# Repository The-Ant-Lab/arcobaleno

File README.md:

# Arcobaleno<br/>A micropython development board made with The Ant.

This is our first complete project made with The Ant CNC machine.  
It is a development board designed by us and intended to be used with micropython.  

In this repository and in this video [The Ant + Micropython = ARCOBALENO](https://youtu.be/vV_R-Mp-2kI), you will find all the related information.  

If you want to realize the board with The Ant see the hardware folder.  
If you have already built the board and you want to use it see the firmware folder.  

If you liked this project and you want to help us develop new interesting projects, please consider donating using the paypal button here:

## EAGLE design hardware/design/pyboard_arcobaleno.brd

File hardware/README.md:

The hardware section is structured as follows:

- design, that contains the schematic and the board layout;
- cam, that contains the CAM outputs of the whole board, comprising gerbers and drill files.
- gcodes, that contains all the gcodes needed to execute the board machining with The Ant (see [here](https://www.youtube.com/channel/UCX44z-SSL7LzcB4xxgUdHHA)).

Before using the gcode files, read carefully the README in the gcodes folder.

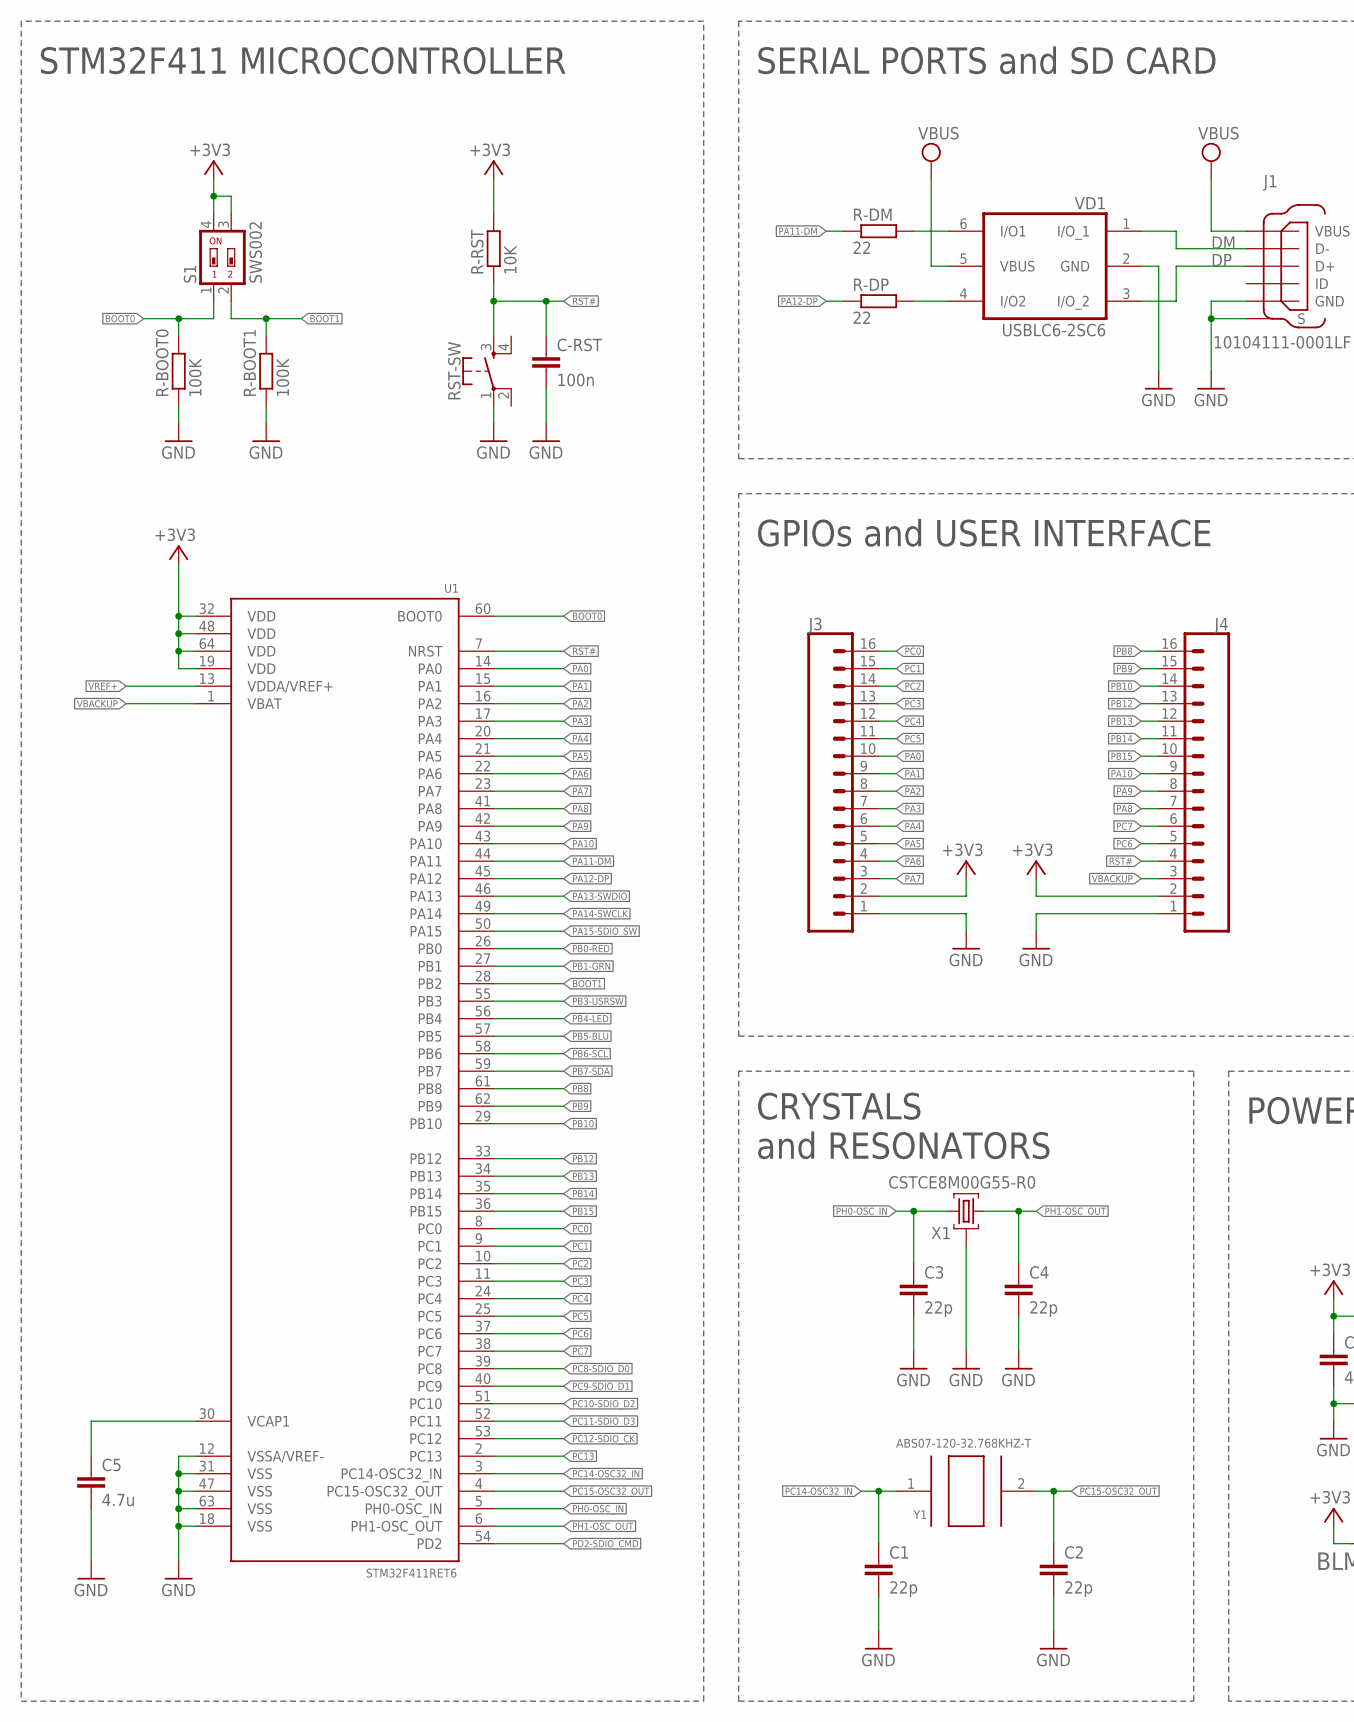
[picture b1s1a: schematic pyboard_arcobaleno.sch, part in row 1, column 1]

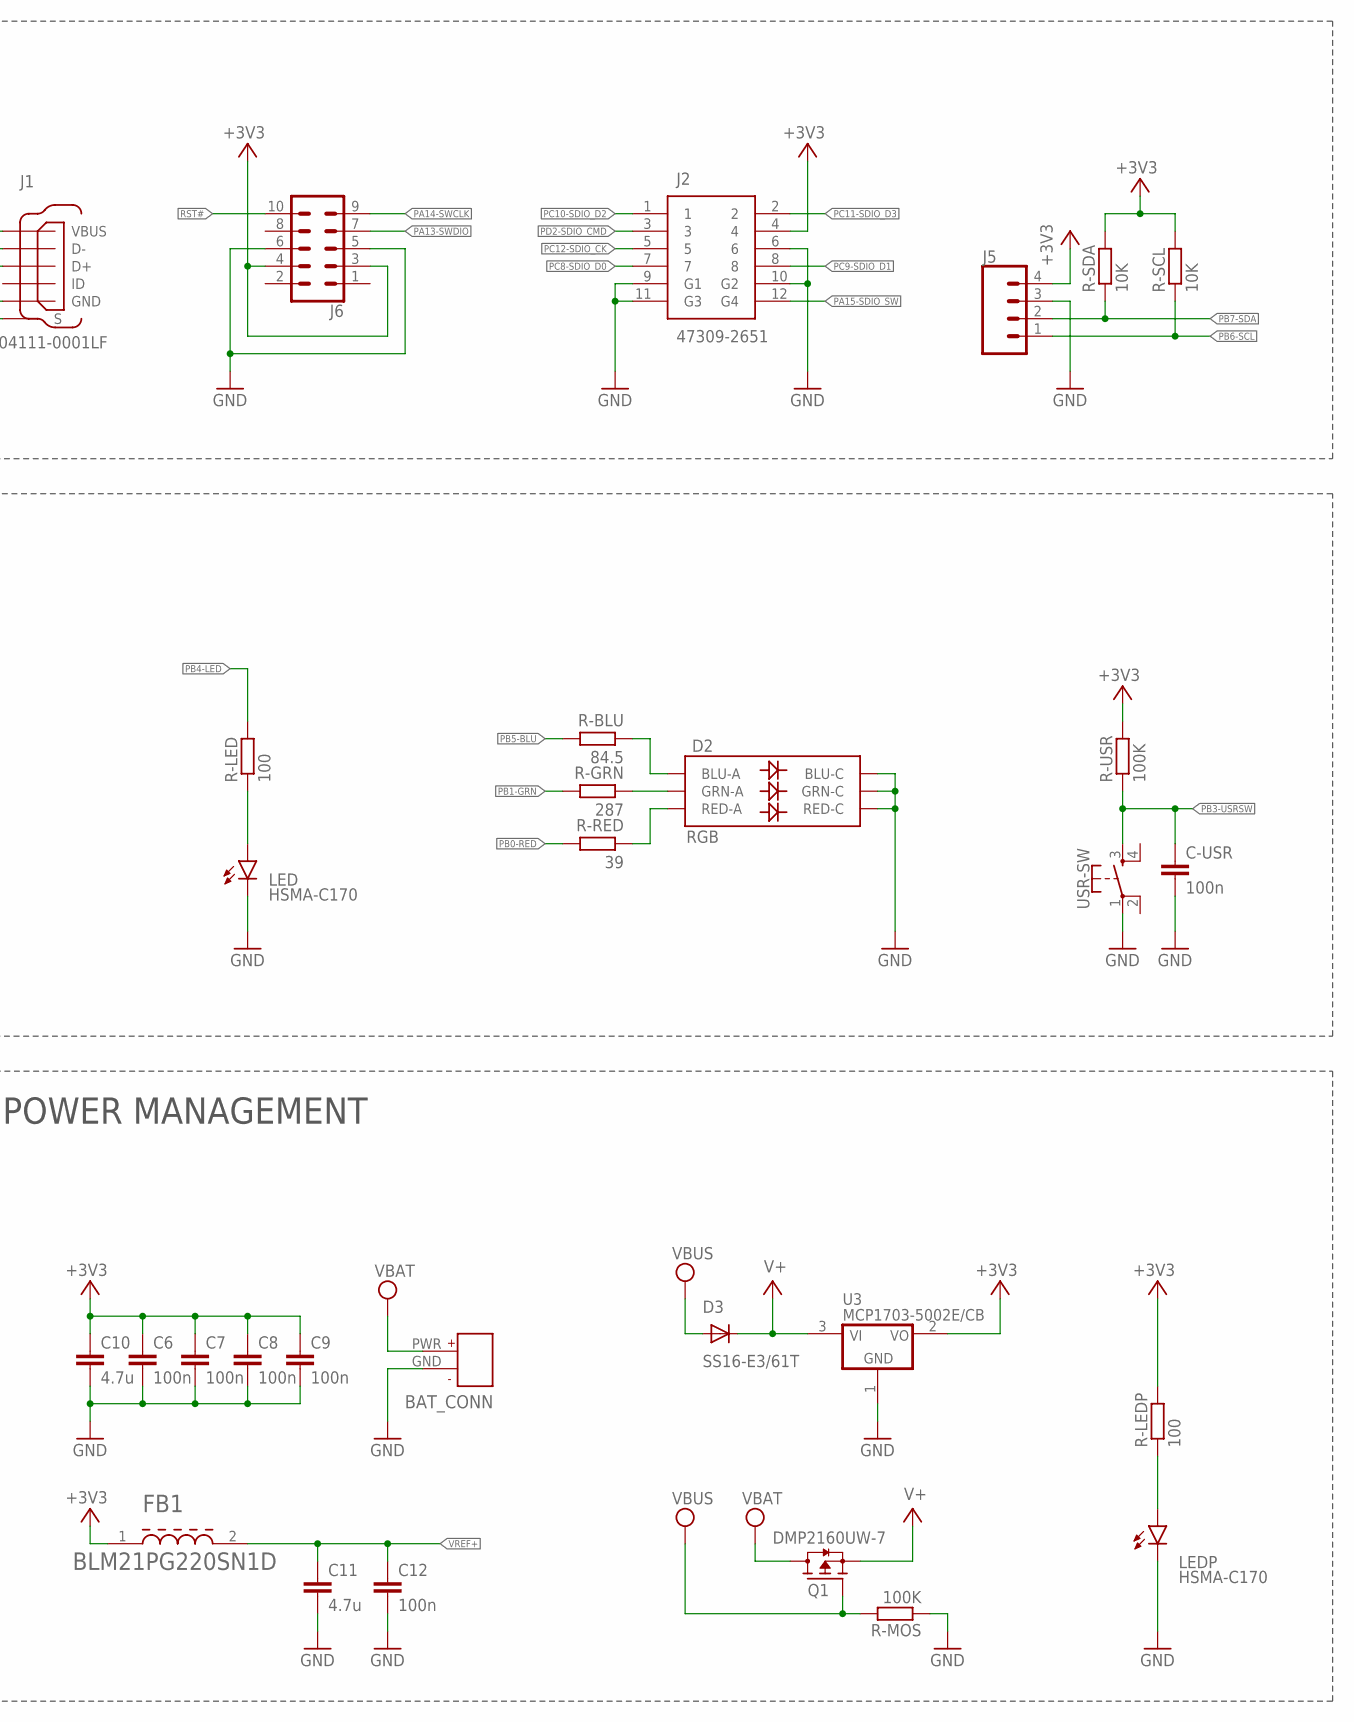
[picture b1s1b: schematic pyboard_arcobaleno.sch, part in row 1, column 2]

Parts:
BAT_CONN: JST_PH_2PIN
C1, C2, C3, C4: 22p; C0603
C5, C10, C11: 4.7u; C1608
C6, C7, C8, C9, C12: 100n; C0603
C-RST: 100n; C0603
C-USR: 100n; C0603
D2: RGB; PLCC-6-LED
D3: SS16-E3/61T; DO214AA
FB1: MURATA_BLM21PG220SN1DMURATA_BLM21PG220SN1D_0_0; MURATA_BLM21PG220SN1D_0
J1: 10104111-0001LF; FRAMATOME_10104111-0001LF
J2: 47309-2651
J3, J4: CONN_16; 1X16
J5: CONN_04; 1X04
J6: CONN_05X2PTH; 2X5
LED: HSMA-C170; CHIPLED_0805
LEDP: HSMA-C170; CHIPLED_0805
Q1: DMP2160UW-7; SOT65P210X110-3N
R-BLU: 84.5; R0603
R-BOOT0, R-BOOT1: 100K; R0603
R-DM: 22; R0603
R-DP: 22; R0603
R-GRN: 287; R0603
R-LED: 100; R0603
R-LEDP: 100; R0603
R-MOS: 100K; R0603
R-RED: 39; R0603
R-RST: 10K; R0603
R-SCL: 10K; R0603
R-SDA: 10K; R0603
R-USR: 100K; R0603
RST-SW: MOMENTARY-SWITCH-SPST-2-SMD-5.2MM; TACTILE_SWITCH_SMD_5.2MM
S1: SWS002; SMS-002
U1: STM32F411RET6; QFP50P1200X1200X160-64N
U3: MCP1703-5002E/CB; SOT23A_MICROCHIP_CB
USR-SW: MOMENTARY-SWITCH-SPST-2-SMD-5.2MM; TACTILE_SWITCH_SMD_5.2MM
VD1: USBLC6-2SC6; SOT-23-6L
X1: CSTCE8M00G55-R0
Y1: ABS07-120-32.768KHZ-T; XTAL_ABS07-120-32.768KHZ-T

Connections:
+3V3: C6.1, C7.1, C8.1, C9.1, C10.1, FB1.1, J2.4, J3.2, J4.2, J5.4, J6.3, J6.4, R-LEDP.2, R-RST.2, R-SCL.2, R-SDA.2, R-USR.2, S1.3, S1.4, U1.19 (VDD), U1.32 (VDD), U1.48 (VDD), U1.64 (VDD), U3.2 (VO)
BOOT0: R-BOOT0.2, S1.1, U1.60 (BOOT0)
BOOT1: R-BOOT1.2, S1.2, U1.28 (PB2)
DM: J1.2 (D-), VD1.1 (I/O_1)
DP: J1.3 (D+), VD1.3 (I/O_2)
GND: BAT_CONN.GND, C1.2, C2.2, C3.2, C4.2, C5.2, C6.2, C7.2, C8.2, C9.2, C10.2, C11.2, C12.2, C-RST.2, C-USR.2, D2.CB (BLU-C), D2.CG (GRN-C), D2.CR (RED-C), J1.5 (GND), J1.6 (S), J1.7 (S), J1.8 (S), J1.9 (S), J2.6, J2.9 (G1), J2.10 (G2), J2.11 (G3), J3.1, J4.1, J5.3, J6.5, J6.6, LED.C, LEDP.C, R-BOOT0.1, R-BOOT1.1, R-MOS.1, RST-SW.1, U1.12 (VSSA/VREF-), U1.18 (VSS), U1.31 (VSS), U1.47 (VSS), U1.63 (VSS), U3.1 (GND), USR-SW.1, VD1.2 (GND), X1.2 (GND)
unnamed: C5.1, U1.30 (VCAP1)
unnamed: R-DM.2, VD1.6 (I/O1)
unnamed: R-DP.2, VD1.4 (I/O2)
unnamed: LED.A, R-LED.1
unnamed: LEDP.A, R-LEDP.1
unnamed: D2.AB (BLU-A), R-BLU.1
unnamed: D2.AG (GRN-A), R-GRN.1
unnamed: D2.AR (RED-A), R-RED.1
PA0: J3.10, U1.14 (PA0)
PA1: J3.9, U1.15 (PA1)
PA2: J3.8, U1.16 (PA2)
PA3: J3.7, U1.17 (PA3)
PA4: J3.6, U1.20 (PA4)
PA5: J3.5, U1.21 (PA5)
PA6: J3.4, U1.22 (PA6)
PA7: J3.3, U1.23 (PA7)
PA8: J4.7, U1.41 (PA8)
PA9: J4.8, U1.42 (PA9)
PA10: J4.9, U1.43 (PA10)
PA11-DM: R-DM.1, U1.44 (PA11)
PA12-DP: R-DP.1, U1.45 (PA12)
PA13-SWDIO: J6.7, U1.46 (PA13)
PA14-SWCLK: J6.9, U1.49 (PA14)
PA15-SDIO_SW: J2.12 (G4), U1.50 (PA15)
PB0-RED: R-RED.2, U1.26 (PB0)
PB1-GRN: R-GRN.2, U1.27 (PB1)
PB3-USRSW: C-USR.1, R-USR.1, U1.55 (PB3), USR-SW.3
PB4-LED: R-LED.2, U1.56 (PB4)
PB5-BLU: R-BLU.2, U1.57 (PB5)
PB6-SCL: J5.1, R-SCL.1, U1.58 (PB6)
PB7-SDA: J5.2, R-SDA.1, U1.59 (PB7)
PB8: J4.16, U1.61 (PB8)
PB9: J4.15, U1.62 (PB9)
PB10: J4.14, U1.29 (PB10)
PB12: J4.13, U1.33 (PB12)
PB13: J4.12, U1.34 (PB13)
PB14: J4.11, U1.35 (PB14)
PB15: J4.10, U1.36 (PB15)
PC0: J3.16, U1.8 (PC0)
PC1: J3.15, U1.9 (PC1)
PC2: J3.14, U1.10 (PC2)
PC3: J3.13, U1.11 (PC3)
PC4: J3.12, U1.24 (PC4)
PC5: J3.11, U1.25 (PC5)
PC6: J4.5, U1.37 (PC6)
PC7: J4.6, U1.38 (PC7)
PC8-SDIO_D0: J2.7, U1.39 (PC8)
PC9-SDIO_D1: J2.8, U1.40 (PC9)
PC10-SDIO_D2: J2.1, U1.51 (PC10)
PC11-SDIO_D3: J2.2, U1.52 (PC11)
PC12-SDIO_CK: J2.5, U1.53 (PC12)
PC13: U1.2 (PC13)
PC14-OSC32_IN: C1.1, U1.3 (PC14-OSC32_IN), Y1.1
PC15-OSC32_OUT: C2.1, U1.4 (PC15-OSC32_OUT), Y1.2
PD2-SDIO_CMD: J2.3, U1.54 (PD2)
PH0-OSC_IN: C3.1, U1.5 (PH0-OSC_IN), X1.1 (INPUT)
PH1-OSC_OUT: C4.1, U1.6 (PH1-OSC_OUT), X1.3 (OUTPUT)
RST#: C-RST.1, J4.4, J6.10, R-RST.1, RST-SW.3, U1.7 (NRST)
V+: D3.C, Q1.2 (S), U3.3 (VI)
VBACKUP: J4.3, U1.1 (VBAT)
VCC: D3.A, J1.1 (VBUS), Q1.1 (G), R-MOS.2, VD1.5 (VBUS)
VEE: BAT_CONN.PWR, Q1.3 (D)
VREF+: C11.1, C12.1, FB1.2, U1.13 (VDDA/VREF+)

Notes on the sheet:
STM32F411 MICROCONTROLLER
SERIAL PORTS and SD CARD
GPIOs and USER INTERFACE
CRYSTALS and RESONATORS
POWER MANAGEMENT

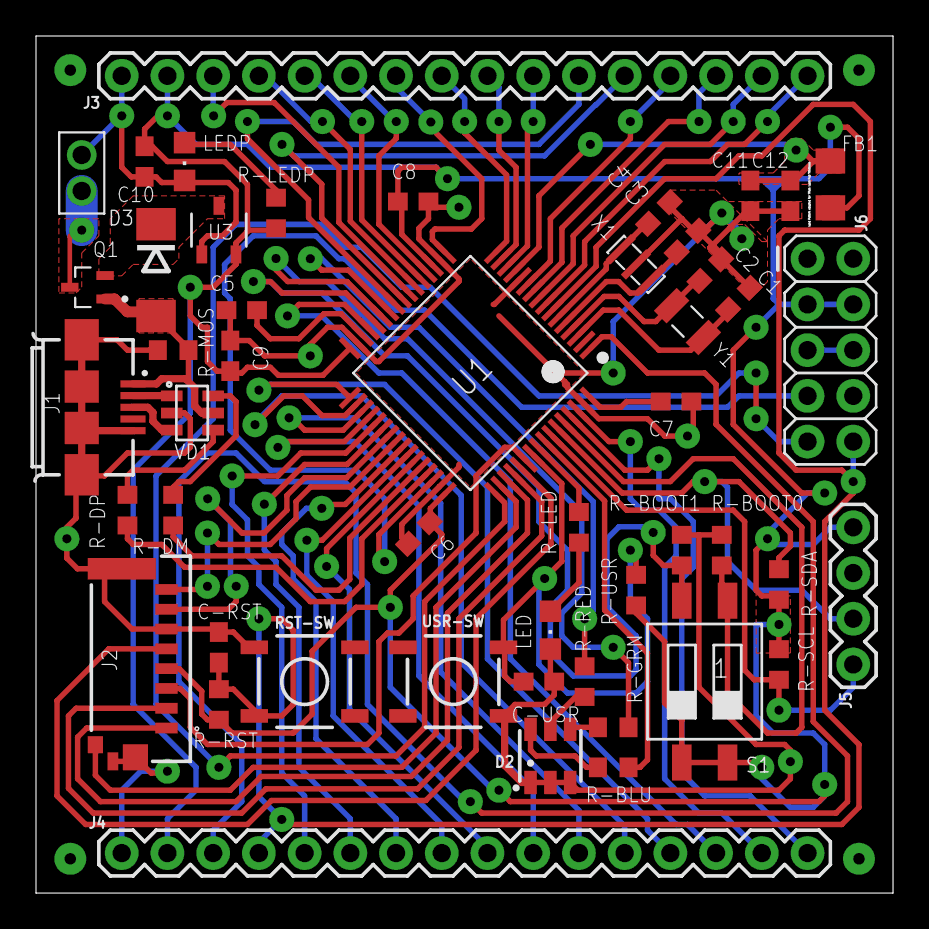
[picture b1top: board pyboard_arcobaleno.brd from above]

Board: 2 copper layers, 47.6 x 47.6 mm, 49 parts (0 on the bottom side), 68 nets.

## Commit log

2019-11-27 Adding arcobaleno config folder, arcobaleno built micropython files, micropython submodule
2019-11-27 Added hardware license.
2019-11-27 Added README for hardware folder.
2019-11-27 Updated README.
2019-11-27 Create LICENSE
2019-11-27 Add firmware license.
2019-11-27 Correct folder structure description
2019-11-27 Added The Ant machining gcode files
2019-11-27 README created
2019-11-27 Added Arcobaleno board design and CAM output files
2019-11-27 Small README corrections.
2019-11-27 Updated video link.
2019-11-28 Correction of wrong Alternate Function numbers.
2019-11-28 Draft of README for firmware.
2020-02-18 Updated micropython submodule to latest version, since they corrected the bug on sd card mount.
2020-02-22 Added PINOUT drawings
2020-06-17 Adding Arcobaleno Plus configurationa and built artifacts

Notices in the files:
parts and their libraries:
SparkFun-Switches: Licensing: Creative Commons ShareAlike 4.0 International - https://creativecommons.org/licenses/by-sa/4.0
